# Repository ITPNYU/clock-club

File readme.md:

# *"The first rule of Clock Club is that no one checks the time at Clock Club."*

## About This Repository

This repo is written with students and scholars of interactive design in mind. It's a collection of materials we've gathered for our own projects and interest in the subject of time. There are software examples of how to make clocks here, microcontroller-driven hardware examples, and fabrication examples of how to make hands and mechanisms. There are also readings and links to other material we've found useful.

## Who We Are

Clock Club started at NYU's [ITP](https://itp.nyu.edu) in about 2016 because a handful of us like making timepieces and wanted external motivation and convesation to work on them. The group includes designers, programmers, electronics hobbyists, fabricators, and scholars.

## What You Need To Know

We assume you're interested in time and timekeeping, probably have a background in interactive design, but aren't necessarily an engineer or professional programmer. You know a little about computer programming. Examples are written in a few programming frameworks that are common in interaction design programs. For further reading on some of the basics we assume, you might want to check out the [ITP Physical Computing Site](https://itp.nyu.edu/physcomp/), the [ITP Fabrication Site](https://itp.nyu.edu/fab/), or the [ITP Intro to Computational Media site](https://github.com/ITPNYU/ICM-2018).

## Site Organization

The site is organized into the following sections:

* [Projects](projects) - clocks, mechanisms, or other time-related examples that we've built, with instructions and/or source material
* [Bibliography](bibliography) - further reading on time and clocks
* [Timepieces](works) - examples of clocks, watches, and other time-related devices, sculptures, buildings, etc.
* [Organizations](organizations) - societies, foundations, schools, and other time-related organizations
* [Tools](tools) - software and hardware tools that we've used for timepieces
* [Parts and Suppliers](parts) - places to get stuff to make timepieces.
* [Notes](notes) - things that have not been organized elsewhere. _(Contributors: please move things from here to other sections when you see where they belong)_

## Contributors

Contributors to this site include Ben Light, Jeff Feddersen, Tom Igoe, Nuntinee Tansrisakul, Arnab Chakravarty, Che-Wei Wang, Yeseul Song, and Will Odom. 

If you're looking for something to add, see the [issues list](https://github.com/ITPNYU/clock-club/issues/) for to-do items.

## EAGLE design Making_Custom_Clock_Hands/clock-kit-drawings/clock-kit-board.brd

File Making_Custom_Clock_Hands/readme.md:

# Making Custom Clock Hands

For many different clock designs, we've been using cheap analog clock movements that you can buy in [hobby stores](https://www.michaels.com/075in-clock-movement-kit-with-small-hands-by-artminds/10475422.html) or online from sources like [Klockit](https://www.klockit.com). These clock movements have fairly standardized shaft dimensions for the hour, minute, and second hands, and you can buy a [variety of hands](https://www.michaels.com/metal-clock-hands-by-recollections/10435215.html) for them as well. We wanted to make our own hands, and experimented with milling them using an [Othermill](https://othermachine.co/), a desktop CNC mill.

The details here refer to the [Quartex Clear Clock Movement](https://www.klockit.com/quartexr-clear-quartz-clock-movement.html) and other Quartex movements from [Klockit](https://www.klockit.com/).

[Link to repository files](https://github.com/ITPNYU/clock-club/tree/main/Making_Custom_Clock_Hands)

## Materials

* 0.4mm brass
* Double Stick Tape
* Copper circuit board
* Acetone

## Measure The Clock Shafts

They're not all exactly the same. Here are the general dimensions we found for three or four different models:
* **hour hand**: about 5mm diameter, slightly tapered to provide tolerance for different hand designs
* **minute hand**: about 3.3mm diameter, with two parallel flatted sides about 2.7mm apart
* **second hand**: a tapered shaft running from about 0.9mm to 1mm diameter. Most second hands are held on with a hollow pin that has a 1mm inner diameter, about 2.2mm outer diameter.

The dimensions of the shafts varies from manufacturer to manufacturer and model to model, however, so measure the specific one you're using with good calipers. With the material we used, an error of about 0.1 - 0.2mm was workable.

If you're cutting hands on a laser cutter, err on the small side. The kerf of the laser beam will make your holes a bit bigger. The acrylic second hand would not hold to the center pin well, so we used a little glue to hold it on.

Reference hands cut from 1/8-inch acrylic on a laser cutter.

Detail of the minute hand.

Detail of the second hand.

All three hands on a clock.

## Examine Existing Hands

The hands of the clock kits we've been buying are generally made from a slightly thinner metal than we used to make our own. They are often rolled to provide more stiffness. The hour hands tend to have rolled edges on the center hole to prevent them from sagging, and the second hands are generally counterweighted to compensate for their length. All of these characteristics contribute to making the hands more stable and to stay more level when on the shaft. Since our hands are flat, we have to compensate. Making the center holes slightly smaller to make the press-fit tighter helped. We're making a clock with very small hands, so that also helped. We still chose to counter-weight the second hand.

The center pin on the second hand is the only feature we haven't yet duplicated. We took the center pin from an existing second hand for our hands.

Store bought hands. Note the rounding of the edges and the center hole in the hour hand, and the center pin on the  second hand.

Custom milled hands in progress. Note that they are totally flat, unlike the store hands. This requires tighter shaft holes.

## Draw the Hands

In designing our hands, the most important lesson was that fillets are our friends. We used a 1/16" bit to mill the hands, so we made sure to fillet the connections between elements, so the bit could turn corners easily.

Drawing of the minute hand, with fillets' radius shown.

## Mill the Hands

To mill the hands, we attached the bronze sheet to a one-sided copper-clad board for making printed circuits. It worked as an effective spoil board. We attached the bronze to the board and the board to the mill's table with double-stick tape. Then we milled the hands with a 1/16" bit. Afterwards, an acetone bath for 3 minutes made it easier to remove the hands from the board.
When removing the hands, we learned to remove gently, from the side, not from from the end.

This copper-clad PCB was used for several iterations of hands.

## Finishing

We tumbled the hands in a barrel of brass screws and nuts overnight to soften the edges. It smoothed the edges off the hands nicely, and didn't bend even the most delicate hands, which was a pleasant surprise.

Hands mounted on the clock shaft for fit before tumbling.

A collection of brass hands after tumbling in a barrel of brass screws.

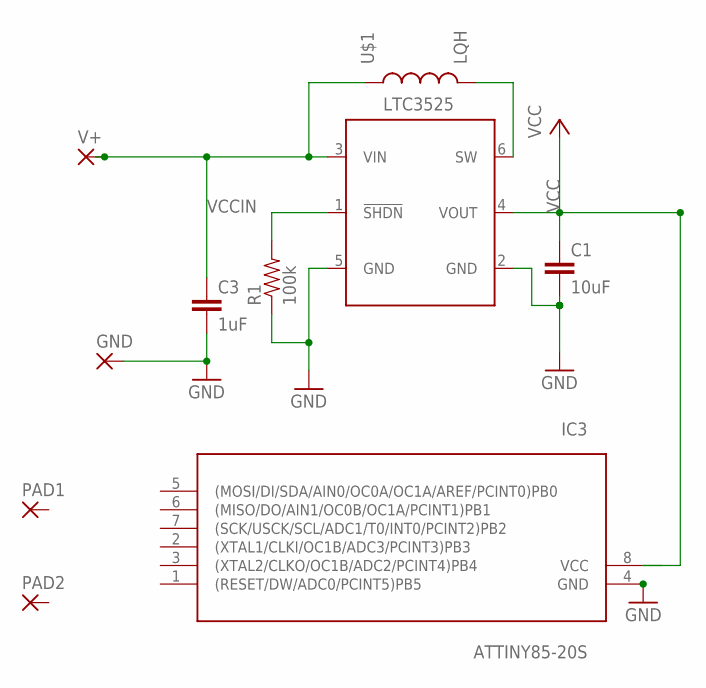
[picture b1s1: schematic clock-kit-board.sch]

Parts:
C1: 10uF; 0805
C3: 1uF; 0805
GND: SMD5; SMD2,54-5,08
IC3: ATTINY85-20S; SOIC8
PAD1, PAD2: 2,54/1,1
R1: 100k; 0805
U$1: LQH; LQH32
U$3: LTC3525; SC70-6L
V+: SMD5; SMD2,54-5,08

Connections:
GND: C1.2, C3.2, GND.1, IC3.4 (GND), R1.1, U$3.2 (GND), U$3.5 (GND)
unnamed: U$1.2, U$3.6 (SW)
SW: R1.2, U$3.1 (!SHDN)
VCC: C1.1, IC3.8 (VCC), U$3.4 (VOUT)
VCCIN: C3.1, U$1.1, U$3.3 (VIN), V+.1

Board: 2 copper layers, 10 parts (0 on the bottom side), 5 nets, no tracks yet.

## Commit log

2016-04-30 Initial commit, readme.md
2016-04-30 List formatting
2016-05-01 Added more links
2016-05-01 added P5.js clock dir and clock001
2016-05-01 updates to clock001
2016-05-26 Initial edit test
2016-05-26 Added more links and resources
2016-05-26 Some organization of links and parts list
2016-05-26 Formatting
2016-05-26 Added suncalc library link
2016-05-28 added neoPixelClock001
2016-06-15 Added links, info, and parts that came up in class
2016-07-30 Clock hands update
2016-07-30 Added links to the readMe
2017-05-29 added SunMoonClock
2017-06-16 Some notes from 6/15 meeting
2017-06-26 Added hand designs for clock kit shafts in Vectorworks, EPS
2017-06-26 added notes on milling custom hands
2017-06-27 added to notes on milling hands
2017-06-28 updated hand milling notes
2017-09-11 added simple Arduino clock control
2017-12-03 added ClocKit standard shafts
2018-04-22 updated neoPixel001 example
2018-04-22 started to consolidate LED and p5.js examples in one directory
2018-04-22 removed ring clock
2018-04-22 removed incomplete example from programmable LED clocks
2018-04-22 added explainer for programmable LED clocks
2018-04-22 added compileTimeSet and StringTimeSet examples
2018-04-22 update to StringTimeSet
2018-04-22 added PushbuttonTimeSet
2018-04-22 Moved time setting examples into their own directory
2018-04-22 started readme on programmable LED examples
2018-04-22 slight changes to time setting page
2018-04-22 changed time setting markdown page to a readme
2018-04-22 changed programmable LED markdown to a readme
2018-04-22 Moved clock hands resources to one directory and updated main readme
2018-04-22 moved images for custom clock hands
2018-04-22 gitignore
2018-04-22 added p5.js readme
2018-04-22 corrected p5.js readme
2018-05-01 Test update on new repo (plus corrected typo)
2018-05-04 New design
    New files for new 2 stepper design
2018-05-04 New moire clock
    Adding new moire clock
2018-05-04 house keeping
    moving old files around
2018-05-05 added Raspberry Pi clock control
2018-05-05 added RTC analog clock example
2018-05-05 added Uno analog clock control
2018-05-05 removed old analog control example
2018-05-05 removed old timesetting markdown
2018-05-05 Ana,og clock control readme
2018-05-05 moved readme
2018-05-05 updated readme. image files for analog clock control
2018-05-05 uodated readme
2018-05-05 readme
2018-05-05 Added schematic for analog clock control
2018-05-05 updated analog clock control readme
2018-05-05 updated readme for analog clock control
2018-05-05 updated analog control schematic
2018-05-05 One more time
2018-05-05 One more analog clock schematic update
2018-05-05 last analog clock push
2018-05-06 node.js analog clock readme
2018-05-06 updarted main readme
2018-05-07 Assembly Instructions
    More info for assmebly instructions
2018-05-07 Assembly Instructions
    update
2018-05-07 Test
    test
2018-05-08 added Clock Animation Test
2018-05-08 added html preview for clock animation test
2018-05-22 added shaft templates for clock hands
2018-05-24 VID28-05 footprint file in progress
2018-05-31 added Analog clock assembly page.
2018-05-31 Updated clock hand tutorial
2018-05-31 image
2018-05-31 markdown layout edits
2018-06-02 Added Geared to the Starts reference
2018-06-02 no message
2018-06-03 Added mooncalc and planet position page in references
2018-06-03 Establish Example directory with info on other interesting clocks. Maybe this augments/incorporates the Inspiration links currently in the readme
2018-06-03 Added img subdirectory in Examples, populated with some initial images
2018-06-03 Added images from Arielle, Ben, and Jeff
2018-06-03 added clock-kit hand files
2018-06-03 moved clock kit hands files
2018-06-03 added center shaft size
2018-06-06 updated clock control
2018-06-18 updated clock animation test
2018-06-18 clock control schematic
2018-06-19 updated clock animation test to adjust hour hand better
2018-06-20 started bibliography
2018-06-22 updated bibliography and readme
2018-06-22 biblio update
2018-06-22 readme update
2018-06-24 Added new suppliers to readme
2018-06-25 added Riskin book
2018-06-25 Moved inspirational works to their own page
2018-11-26 added RTC examples
2018-12-02 added ePaper example to RTC Clock examples
2018-12-18 turned instructions.txt into readme.md for readablity
2019-01-22 Added decimal time JS clock
2019-01-22 updates to decimal clock
2019-01-26 added colorClock, in progress
2019-02-15 added colorClock and notes on Christer Nilsson's bezier clock
2019-03-11 added calculation of daylight savings and local time from UTC and timezone, for microcontrollers
2019-04-30 added WiFiTimeSet example
2019-05-30 added WifiTimeDriftCheck and updated WiFiTimeSet
2019-05-30 moved timeDriftCheck to RTC examples, added timeDriftCheckSD
2020-01-21 Update to VID28-05 work
2020-01-21 Added TabletopClock directory
2020-01-21 updated main readme and tabletop clock readme
2020-02-11 Update TabletopClock001.ino
    Fixed direction of encoder and setting hand color
2020-06-03 added What Not To Do clock
2020-06-06 update can clock hands
2020-06-26 Set theme jekyll-theme-minimal
2020-06-26 pages updates
2020-06-26 more pages updates
2021-07-08 Updated and reorganized
2021-07-08 Bibiliography and works updates
2021-07-08 Updates and cleanups
2021-10-12 added clock setter p5.js and Arduino example
2021-10-12 changed name of main branch in all references
2021-10-14 update clock002
2021-10-25 added clock003
2023-04-09 added timestamps.md
2023-04-09 updated timestamps and layout
2023-04-09 update clock001
2023-04-09 update time setting examples
2023-04-09 update time setting
2023-04-09 Add rtcInterval
2023-04-10 update to interval examples
